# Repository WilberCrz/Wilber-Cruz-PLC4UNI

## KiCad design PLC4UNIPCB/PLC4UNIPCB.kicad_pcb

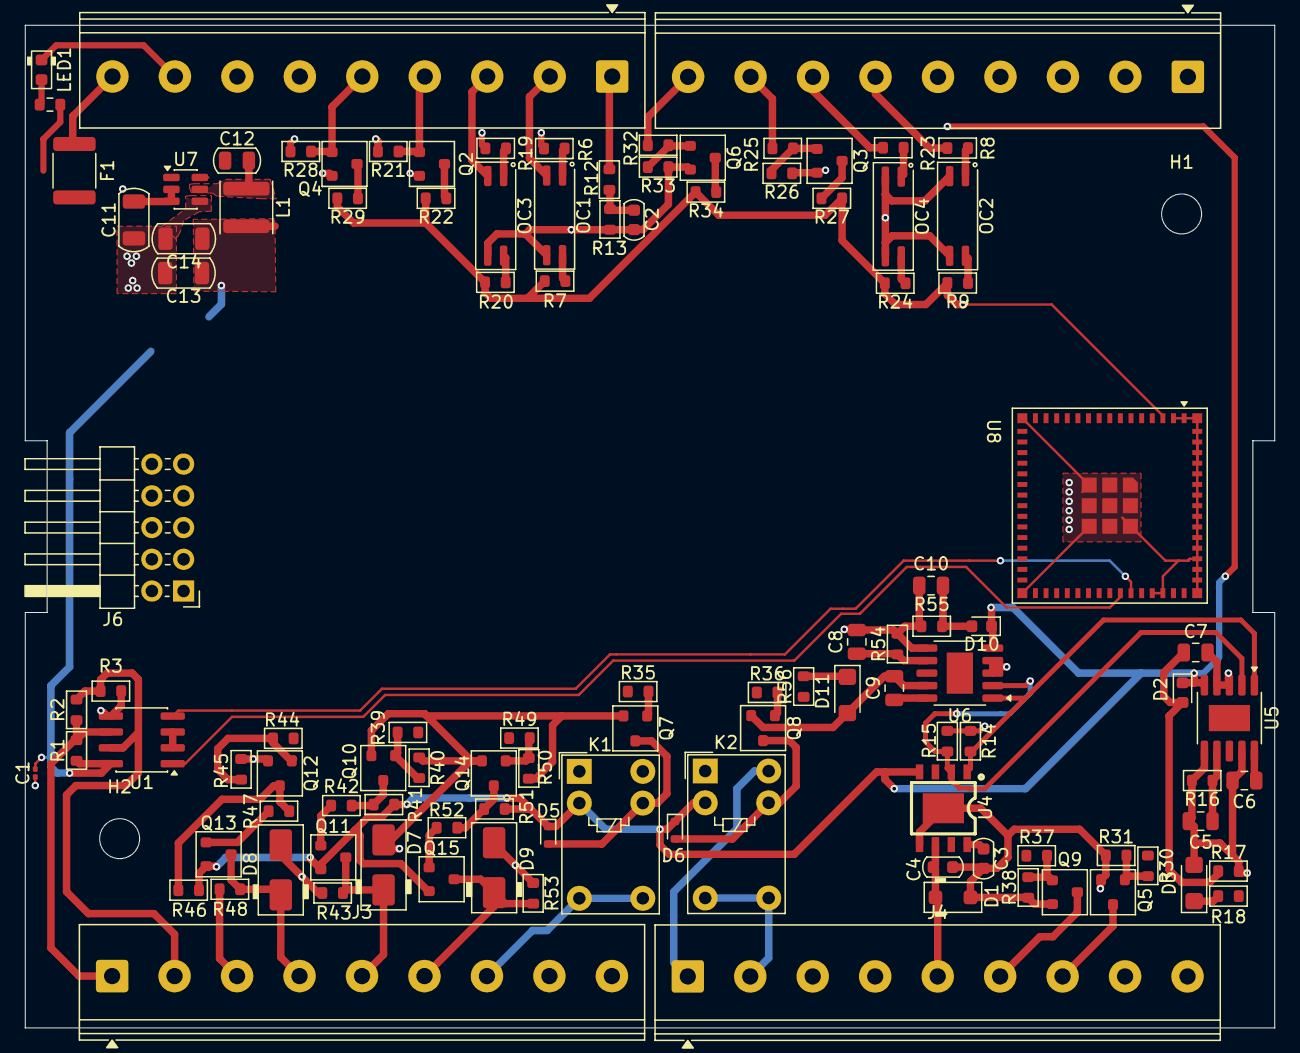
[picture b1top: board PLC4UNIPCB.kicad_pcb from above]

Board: 4 copper layers, 100.0 x 80.2 mm, 113 parts (0 on the bottom side), 82 nets.

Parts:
C1: 100nF; C_0201_0603Metric
C2, C4: 0.1uF; C_0603_1608Metric
C3: 1uF; C_0603_1608Metric
C5, C8: 220pF; C_0805_2012Metric
C6, C7, C9, C10: 1uF; C_0805_2012Metric
C11: 10uF; C_1206_3216Metric
C12: 100nF; C_0805_2012Metric
C13, C14: 22uF; C_1206_3216Metric
D1: TVA; D_SOD-123F
D2, D10: D_Zener; D_0603_1608Metric
D3, D11: SMF24A; D_SMF
D5, D6: 1N4148WT; D_SOD-523
D7, D8, D9: M7; D_SMA
F1: Fuse; Fuse_1812_4532Metric
H1, H2: MountingHole_M3; MountingHole_3.2mm_M3
J1: Screw_Terminal_9_P3.50mm; TerminalBlock_Phoenix_PT-1,5-9-5.0-H_1x09_P5.00mm_Horizontal
J2, J3, J4: Screw_Terminal_9_P5.00mm; TerminalBlock_Phoenix_PT-1,5-9-5.0-H_1x09_P5.00mm_Horizontal
J6: PINHD_2x5_Male; PinHeader_2x05_P2.54mm_Horizontal
K1, K2: G5V-1; Relay_SPDT_Omron_G5V-1
L1: ANR4030T6R8M; L_APV_ANR4030
LED1: LED_0603_Red; LED_0603_1608Metric
OC1, OC2, OC3, OC4: TLP293; SOP-4_4.4x2.6mm_P1.27mm
Q2, Q3, Q4, Q5, Q6, Q7, Q8, Q9, Q10, Q12, Q14: BC817; SOT-23
Q11, Q13, Q15: MMBT4403; SOT-23
R1, R2, R3, R31, R38, R40, R42, R43, R45, R47, R48, R50, R52, R53: 10k; R_0603_1608Metric
R6, R7, R13, R19, R20, R21, R25, R28, R32: 10K; R_0603_1608Metric
R8, R23: 4.7K; R_0603_1608Metric
R9, R22, R24, R27, R29, R34: 2.4K; R_0603_1608Metric
R12: 20K; R_0603_1608Metric
R14, R15, R41, R46, R51: 4.7k; R_0603_1608Metric
R16, R54: 2.5k; R_0603_1608Metric
R17, R55: 470k; R_0603_1608Metric
R18, R56: 15; R_0603_1608Metric
R26, R33: 47K; R_0603_1608Metric
R30, R35, R36, R37, R39, R44, R49: 2.4k; R_0603_1608Metric
R57: 1k; R_0603_1608Metric
U1: SP3485EN; SOIC-8_3.9x4.9mm_P1.27mm
U4: ESOP-8_L4.9-W3.9-P1.27-LS6.0-BL-EP
U5, U6: SSOP-10-1EP_3.9x4.9mm_P1mm_EP2.1x3.3mm
U7: AP63203WU; TSOT-23-6
U8: ESP32-S3-MINI-1U; ESP32-S2-MINI-1U

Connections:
+3.3V: C1.1, C13.1, C14.1, L1.2, R1.2, R7.1, R9.2, R14.1, R15.1, R20.1, R22.2, R24.2, R27.2, R29.2, R34.2, U1.8 (VCC), U7.1 (FB), U8.3 (3V3)
+24V: F1.1, J1.9
/Board-PLC4UNI-G1W/IN_0-10V: J1.1, R12.1
/Board-PLC4UNI-G1W/IN_NPN: J1.5, Q4.1 (B), R28.2
/Board-PLC4UNI-G1W/IN_NPN1_Opto: J1.3, OC3.2
/Board-PLC4UNI-G1W/IN_NPN2: J1.4, Q2.1 (B), R21.2
/Board-PLC4UNI-G1W/IN_NPN2_Opto: J1.2, OC1.2
/Board-PLC4UNI-G1W/IN_PNP1: J2.9, R32.2
/Board-PLC4UNI-G1W/IN_PNP1_Opto: J2.7, R23.1
/Board-PLC4UNI-G1W/IN_PNP2: J2.8, R25.2
/Board-PLC4UNI-G1W/IN_PNP2_Opto: J2.6, R8.1
/Board-PLC4UNI-G1W/Input_0-10V/ADC_IN_3V3: C2.2, R12.2, R13.1
/Board-PLC4UNI-G1W/Input_NPN1/OUT: Q2.3 (C), R22.1, U8.25 (IO21)
/Board-PLC4UNI-G1W/Input_NPN1_Opto1/OUT: OC1.4, R7.2, U8.32 (IO36)
/Board-PLC4UNI-G1W/Input_NPN1_Opto/OUT: OC3.4, R20.2, U8.31 (IO35)
/Board-PLC4UNI-G1W/Input_NPN/OUT: Q4.3 (C), R29.1, U8.26 (IO26)
/Board-PLC4UNI-G1W/Input_PNP1_Opto/OUT: OC4.4, R24.1, U8.28 (IO33)
/Board-PLC4UNI-G1W/Input_PNP2/OUT: Q3.3 (C), R27.1, U8.34 (IO38)
/Board-PLC4UNI-G1W/Input_PNP2_Opto/OUT: OC2.4, R9.1, U8.29 (IO34)
/Board-PLC4UNI-G1W/Input_PNP/OUT: Q6.3 (C), R34.1, U8.33 (IO37)
/Board-PLC4UNI-G1W/NPN_OUT1: J4.6, Q9.3 (C)
/Board-PLC4UNI-G1W/NPN_OUT2: J4.7, Q5.3 (C)
/Board-PLC4UNI-G1W/OutRelay2/IN: R36.1, U8.6 (IO2)
/Board-PLC4UNI-G1W/Out_0-10V: C4.2, D1.1 (K), J4.5, U4.6 (VOUT)
/Board-PLC4UNI-G1W/OutputRelay1/IN: R35.1, U8.30 (IO48)
/Board-PLC4UNI-G1W/Output_0-10V/SCL: R14.2, U4.1 (SCLK), U5.1 (SCLK), U6.1 (SCLK), U8.13 (IO9)
/Board-PLC4UNI-G1W/Output_0-10V/SDA: R15.2, U4.2 (SDA), U5.2 (SDA), U6.2 (SDA), U8.12 (IO8)
/Board-PLC4UNI-G1W/Output_NPN1/IN: R30.1, U8.4 (IO0)
/Board-PLC4UNI-G1W/Output_NPN/IN: R37.1, U8.5 (IO1)
/Board-PLC4UNI-G1W/Output_PNP1/IN: R39.1, U8.38 (IO42)
/Board-PLC4UNI-G1W/Output_PNP2/IN: R49.1, U8.41 (IO45)
/Board-PLC4UNI-G1W/Output_PNP/IN: R44.1, U8.37 (IO41)
/Board-PLC4UNI-G1W/PLC4UNI/USB+: J6.9, U8.24 (USB_D+)
/Board-PLC4UNI-G1W/PLC4UNI/USB-: J6.7, U8.23 (USB_D-)
/Board-PLC4UNI-G1W/PLC4UNI/micro_rs485_rx: U1.4 (DI), U8.40 (RXD0)
/Board-PLC4UNI-G1W/PLC4UNI/micro_rs485_tx: U1.1 (RO), U8.39 (TXD0)
/Board-PLC4UNI-G1W/PNP_OUT1: D8.1 (K), J3.4, Q13.3 (C), R48.2
/Board-PLC4UNI-G1W/PNP_OUT2: D7.1 (K), J3.5, Q11.3 (C), R43.2
/Board-PLC4UNI-G1W/PNP_OUT3: D9.1 (K), J3.6, Q15.3 (C), R53.2
/Board-PLC4UNI-G1W/RS485_Module1_protect/~TX/RX: U1.2 (~RE), U1.3 (DE)
/Board-PLC4UNI-G1W/con_RS485_A: J3.1, R1.1, R2.2, U1.6 (A)
/Board-PLC4UNI-G1W/con_RS485_B: J3.2, R2.1, R3.2, U1.7 (B)
/Board-PLC4UNI-G1W/out-common-1: J3.7, K1.5, K1.6
/Board-PLC4UNI-G1W/out-common-2: J4.2, K2.5, K2.6
/Board-PLC4UNI-G1W/out-nc: J3.8, K1.1
/Board-PLC4UNI-G1W/out-no-1: J3.9, K1.10
/Board-PLC4UNI-G1W/out-no-2: J4.1, K2.10
GND: C1.2, C2.1, C3.2, C4.1, C5.2, C6.2, C7.2, C8.2, C9.2, C10.2, C11.2, C13.2, C14.2, D1.2 (A), D3.2 (A2), D7.2 (A), D8.2 (A), D9.2 (A), D11.2 (A2), J1.8, J2.5, J3.3, LED1.1 (K), OC1.3, OC2.2, OC2.3, OC3.3, OC4.2, OC4.3, Q2.2 (E), Q3.2 (E), Q4.2 (E), Q5.2 (E), Q6.2 (E), Q7.2 (E), Q8.2 (E), Q9.2 (E), Q10.2 (E), Q12.2 (E), Q14.2 (E), R3.1, R13.2, R16.2, R17.2, R26.2, R31.1, R33.2, R38.1, R40.1, R43.1, R45.1, R48.1, R50.1, R53.1, R54.2, R55.2, U1.5 (GND), U4.5 (GND), U4.9 (EP), U5.3 (A0), U5.4 (A1), U5.6 (GND), U5.9 (A2), U6.3 (A0), U6.4 (A1), U6.6 (GND), U6.9 (A2), U7.4 (GND), U8.1 (GND), U8.2 (GND), U8.42 (GND), U8.43 (GND), U8.46 (GND), U8.47 (GND), U8.48 (GND), U8.49 (GND), U8.50 (GND), U8.51 (GND), U8.52 (GND), U8.53 (GND), U8.54 (GND), U8.55 (GND), U8.56 (GND), U8.57 (GND), U8.58 (GND), U8.59 (GND), U8.60 (GND), U8.61 (GND), U8.62 (GND), U8.63 (GND), U8.64 (GND), U8.65 (GND)
unnamed: C7.1, D2.2 (A), R17.1
unnamed: D3.1 (A1), R18.2
unnamed: D5.2 (A), K1.9, Q7.3 (C)
unnamed: D6.2 (A), K2.9, Q8.3 (C)
unnamed: C10.1, D10.2 (A), R55.1
unnamed: D11.1 (A1), R56.2
unnamed: LED1.2 (A), R57.1
unnamed: OC1.1, R6.2
unnamed: OC2.1, R8.2
unnamed: OC3.1, R19.2
unnamed: OC4.1, R23.2
unnamed: Q3.1 (B), R25.1, R26.1
unnamed: Q5.1 (B), R30.2, R31.2
unnamed: Q6.1 (B), R32.1, R33.1
unnamed: Q7.1 (B), R35.2
unnamed: Q8.1 (B), R36.2
unnamed: Q9.1 (B), R37.2, R38.2
unnamed: Q10.1 (B), R39.2, R40.2
unnamed: Q10.3 (C), R41.1, R42.1
unnamed: Q11.1 (B), R42.2
unnamed: Q12.1 (B), R44.2, R45.2
unnamed: Q12.3 (C), R46.1, R47.1
unnamed: Q13.1 (B), R47.2
unnamed: Q14.1 (B), R49.2, R50.2
unnamed: Q14.3 (C), R51.1, R52.1
unnamed: Q15.1 (B), R52.2
unnamed: C3.1, U4.8 (V5V)
unnamed: C5.1, R16.1, U5.7 (SET)
unnamed: C6.1, U5.10 (V5V)
unnamed: C8.1, R54.1, U6.7 (SET)
unnamed: C9.1, U6.10 (V5V)
unnamed: C12.1, U7.6 (BST)
unnamed: C12.2, L1.1, U7.5 (SW)
VCC: C11.1, D2.1 (K), D5.1 (K), D6.1 (K), D10.1 (K), F1.2, K1.2, K2.2, Q11.2 (E), Q13.2 (E), Q15.2 (E), R6.1, R19.1, R21.1, R28.1, R41.2, R46.2, R51.2, R57.2, U4.4 (VCC), U5.5 (VCC), U6.5 (VCC), U7.2 (EN), U7.3 (IN)

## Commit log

2025-09-23 Add files via upload
    Actualización del documento.
2025-09-24 Update Tarea2 - Video.txt
    Enlace al video
2025-09-25 Create
2025-09-25 FreeCad
2025-09-25 Video
2025-09-25 FreeCad 208
2025-09-25 SolidEdge 208
2025-10-09 SolidEdge 209
2025-10-09 Kicad con archivo DXF
2025-10-09 Imágenes de baja calidad arregladas.
2025-10-09 Enlace al Video
2025-11-10 Add files via upload
    Actualización de Esquemáticos
2025-12-02 Add files via upload
    Tarea 4
